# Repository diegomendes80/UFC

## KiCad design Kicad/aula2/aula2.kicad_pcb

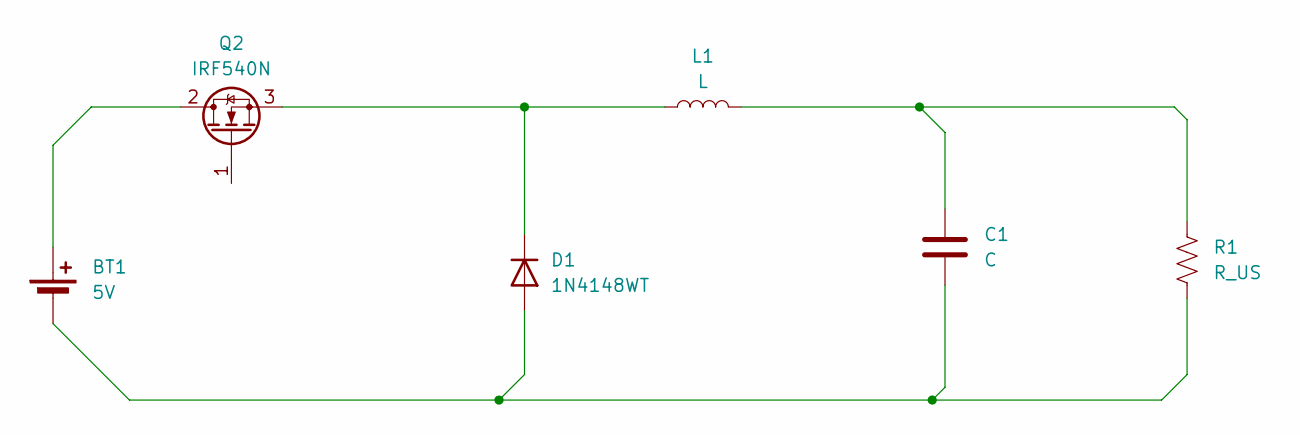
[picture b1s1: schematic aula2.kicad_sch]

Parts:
BT1: 5V; BatteryHolder_Bulgin_BX0123_1xCR123
C1: C; CP_Radial_D12.5mm_P2.50mm
D1: 1N4148WT; D_A-405_P10.16mm_Horizontal
L1: L; L_Axial_L7.0mm_D3.3mm_P10.16mm_Horizontal_Fastron_MICC
Q2: IRF540N; TO-220-3_Vertical
R1: R_US; R_Axial_DIN0207_L6.3mm_D2.5mm_P2.54mm_Vertical

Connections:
unnamed: BT1.1 (+), Q2.2 (D)
unnamed: BT1.2 (-), C1.2, D1.2 (A), R1.2
unnamed: C1.1, L1.2, R1.1
unnamed: D1.1 (K), L1.1, Q2.3 (S)

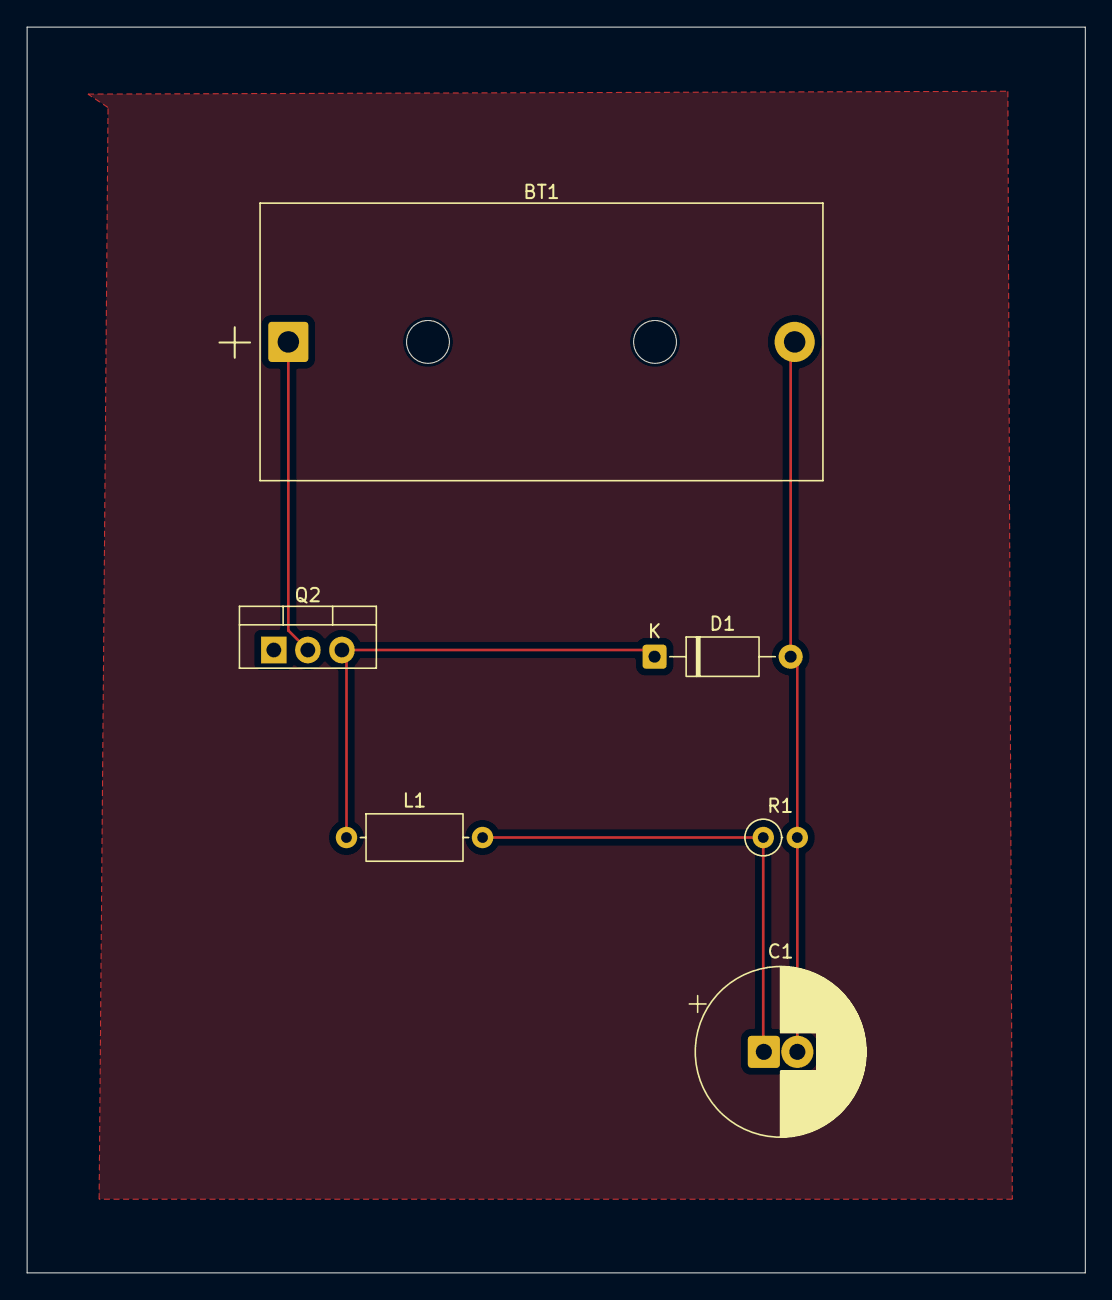
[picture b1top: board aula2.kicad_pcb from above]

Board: 2 copper layers, 79.0 x 93.0 mm, 6 parts (0 on the bottom side), 4 nets.

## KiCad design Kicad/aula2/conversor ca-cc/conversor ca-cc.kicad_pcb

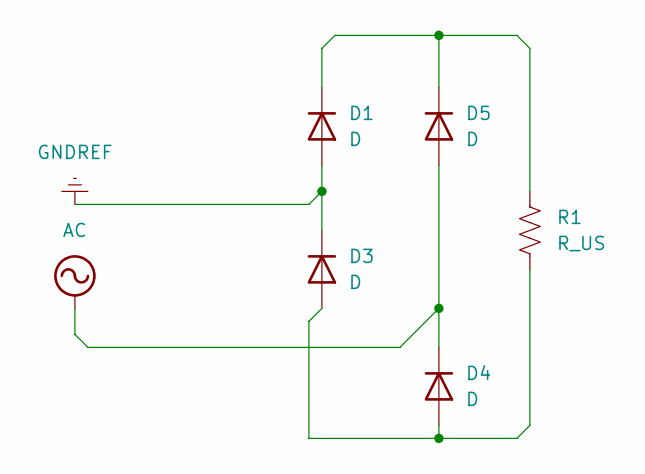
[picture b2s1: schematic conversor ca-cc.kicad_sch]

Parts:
D1, D3, D4, D5: D; D_A-405_P10.16mm_Horizontal
R1: R_US; R_Axial_DIN0207_L6.3mm_D2.5mm_P2.54mm_Vertical

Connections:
AC: D4.1 (K), D5.2 (A)
GNDREF: D1.2 (A), D3.1 (K)
unnamed: D1.1 (K), D5.1 (K), R1.1
unnamed: D3.2 (A), D4.2 (A), R1.2

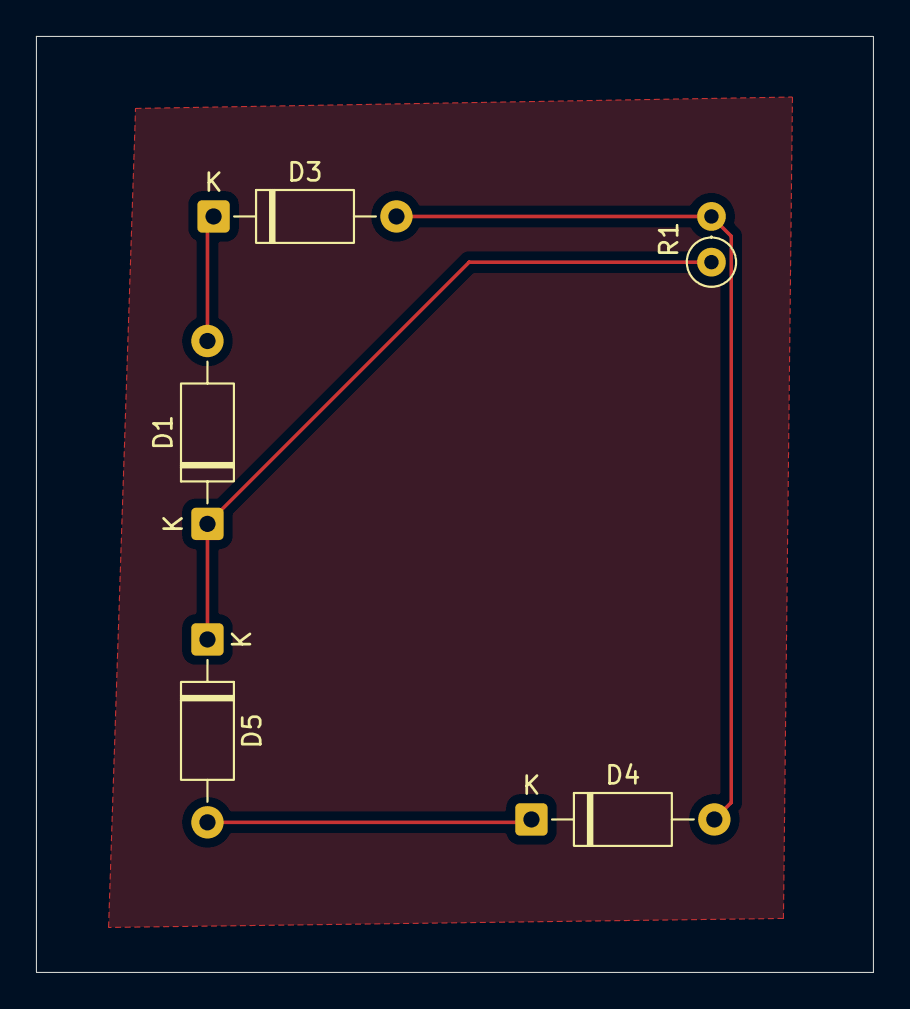
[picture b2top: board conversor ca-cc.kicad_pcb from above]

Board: 2 copper layers, 46.5 x 52.0 mm, 5 parts (0 on the bottom side), 4 nets.

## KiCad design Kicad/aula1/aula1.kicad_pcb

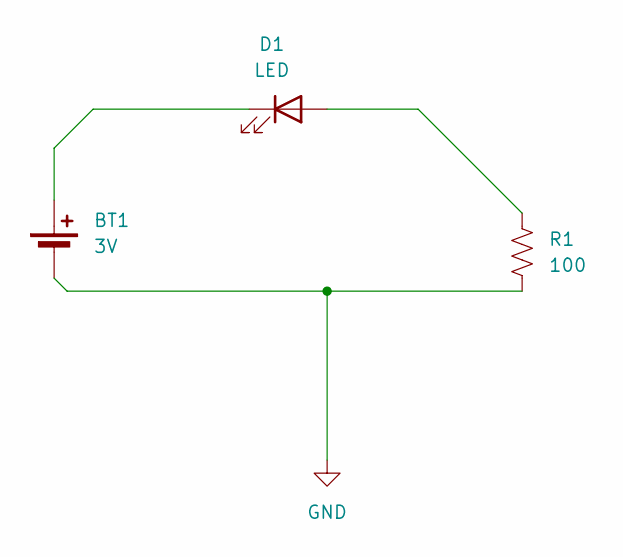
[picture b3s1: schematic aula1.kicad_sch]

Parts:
BT1: 3V; BatteryHolder_Keystone_2466_1xAAA
D1: LED; LED_D5.0mm_IRGrey
R1: 100; R_Axial_DIN0617_L17.0mm_D6.0mm_P30.48mm_Horizontal

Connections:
GND: BT1.2 (-), R1.2
unnamed: BT1.1 (+), D1.1 (K)
unnamed: D1.2 (A), R1.1

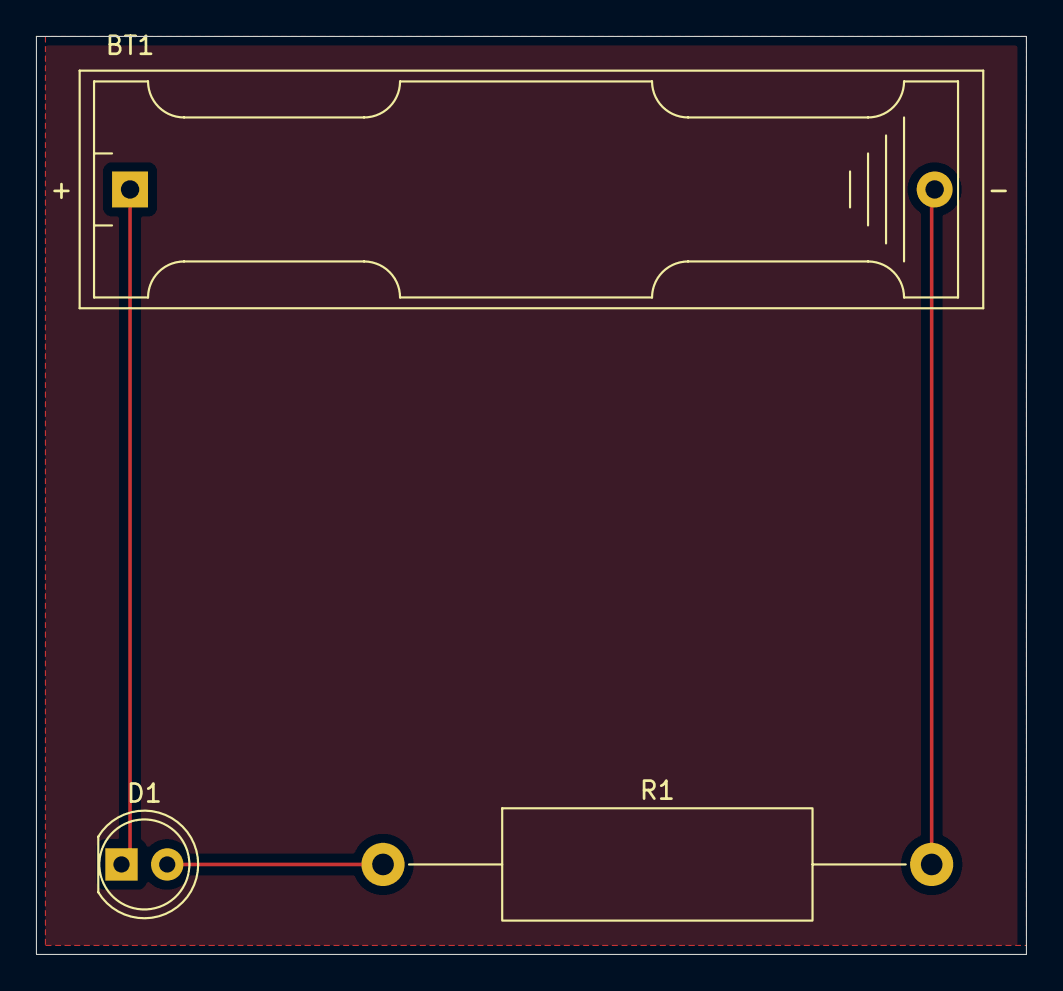
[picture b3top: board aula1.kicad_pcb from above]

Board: 2 copper layers, 55.0 x 51.0 mm, 3 parts (0 on the bottom side), 3 nets.

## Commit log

2024-10-23 Primeira aula de Java
2024-11-11 Algumas aulas de java
    Concertar as pastas dos arquivos
2024-11-13 aula 03 poo
2024-11-18 aula de java uf
2024-11-25 Aula 05 de java
2024-12-15 exercicios java
2025-01-09 Aulas de POO
2025-01-18 alguns exercicios de java
2025-02-04 alguns exercicios de java
    abstract, static, enums, interface e etc
2025-02-05 projeto final POO
    subindo os primeiros arquivos
2025-02-09 começando o front
2025-02-09 Código antes da integração
    Subindo o que fiz do front-end antes de juntar com o back-end
2025-02-10 Primeiro contato com a API
    Consegui fazer a busca de informações com a API. Gerei os cards dos filmes mas ainda estão bugados, Consertar isso
2025-02-11 PQP!
    Vou ter que refazer tudo denovo por que tem que usar Swing
2025-02-12 Reiniciando
    Primeiras implementações com Swing
2025-02-13 Problema na URL Capa
    a url das capas do filme estão sendo passadas erradas
2025-02-13 problema da url resolvido
    Aparentemente se resolveu sozinho quando rodei no outro dia
2025-02-13 Event Listener dos botoes
    Consegui gerar os cads dinamicamente conforme aperto em series ou filmes.
    Criei uma função que desenha os cards, uma que gera os 10 cards e outra que exibe
2025-02-14 Navegação otimizada
    Consegui otimizar a troca de paineis quando clico em filmes ou series. Basicamente eu crio primeiro os cards antes de iniciar o app, que é o que demora, e só fico aidiconando ou removendo dos paineis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
2025-02-14 Agora da pra pesquisar
    Consegui otimizar ainda mais a função criaCards, e também implementei o método que mostra um filme/série buscado
2025-02-15 classe json implementada
    construi os principais métodos que manipulam os jsons do projeto. Ainda faltam alguns, porém o mais básico já foi. Agora, quando pesquiso um filme/serie ele ja insere no json. Além disso não é possiv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
2025-02-16 navegação entre paginas
2025-02-17 Antes de gerar sinopse
2025-02-17 Tela de avaliação quase pronta
    falta adicionar a função de avaliar
2025-02-19 painel de avaliação
    Criei o painel para avaliar. Agora falta criar os cards que expoem as avaliações existentes
2025-02-20 função para mostrar resenhas
    terminei a função que mostra as resenhas existentes. Agora falta implementar a parte de setar uma nova resenha
2025-02-21 nota fica salva
    agora quando avalio um filme, ele é atualizado
2025-02-22 atualização na nota
2025-02-22 logica de atualização de nota
    agora quando estou na tela avaliação e clico em voltar ele verifica se houve uma atualização na midia através da variavel isUpdate. Se for true ele recarrega os cards.
2025-02-22 função de adiconar/remover dos favoritos
    consegui implmentar um botão que remove e adiciona a lista de favoritos
2025-02-22 salva no arquivo json
    salva no arquivo respetivo filmes e series favoritas
2025-02-24 Tela Listas finalizada
    Consertei o bug de alterar a lista de favoritos e não mudar na tela. Agora acho que já terminei tudo, falta só alguns detalhes para arrumar mas o app em si está pronto
2025-02-24 FIM!
    Projeto finalizado, só falta refatorar
2025-02-24 Algumas mudanças nos cards resenhas
2025-02-24 Flick, um bom nome
2025-02-25 Bug duplicar resenhas corrigido
2025-02-25 ultimo commit antes de enviar
2025-03-24 Começando a estudar ED
    estrtuturas de dados
2025-04-03 video aula
2025-05-05 arvores
2025-05-08 exercicios lista de edd
2025-05-11 lista de edd
2025-08-20 exercicios edd
2025-10-10 aulas VHDL
2025-10-15 aulas kicad e vhdl
2026-02-23 exercicios de cana
    f
